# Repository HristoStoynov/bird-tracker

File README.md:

# Bird Tracker

A lightweight GPS + cellular wildlife tracker built around the STM32U031, SIM7080G (NB-IoT/LTE-M), and u-blox SAM-M10Q GNSS module.

## Repository structure

```
firmware/   STM32 firmware
hardware/   KiCad schematics and PCB layout
```

> More updates coming July 2026.

## License

MIT — see [LICENSE](LICENSE).

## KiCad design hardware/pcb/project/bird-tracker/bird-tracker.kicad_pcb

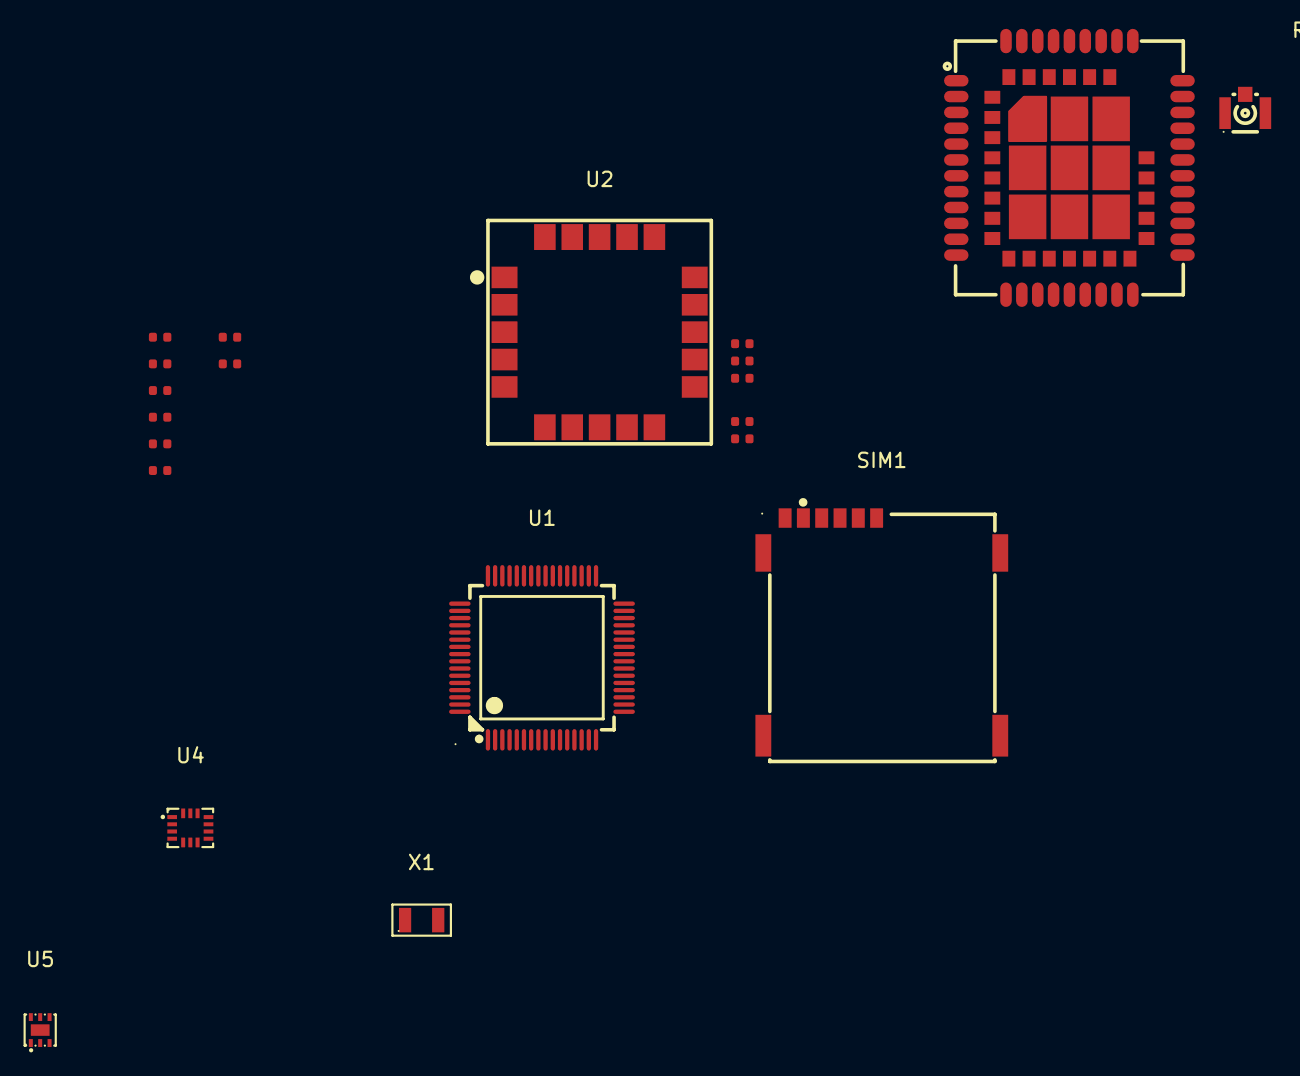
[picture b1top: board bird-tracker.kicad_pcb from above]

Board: 2 copper layers, 21 parts (0 on the bottom side), 9 nets, no tracks yet.

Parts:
C1, C2, C3, C5: 100nF; C_0402
C4: 10uF; C_0402
R1: 22Ω; R_0402
R2, R3: 2.2kΩ; R_0402
R2#2, R3#2, R4: 22kΩ; R_0402
R5, R6: 10kΩ; R_0402
RF1: U.FL-R-SMT; ANT-SMD_U.FL-R-SMT10
SIM1: MICRO SIM 6P H1.35; SIM-SMD_MICRO-SIM-6P-H1.35
U1: STM32U031R8T6; LQFP-64_L10.0-W10.0-P0.50-LS12.0-BL
U2: SAM-M10Q-00B; LCC-20_L15.5-W15.5-P1.90_SAM-M10Q-00B
U3: SIM7080G; LCC-SMD_SIM7080G
U4: LSM6DS3TR; LGA-14_L3.0-W2.5-P0.50-TL
U5: STTS22HTR; DFN-6_L2.0-W2.0-P0.65-BL-EP1.2
X1: ABS07-32.768KHZ-7-T; OSC-SMD_L3.2-W1.5

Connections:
+3.3V: C1.1, C2.1, C3.1, C4.1, C5.1, R2.2, R2#2.2, R3.2, R3#2.2, R5.2, R6.1, U2.2 (V_IO), U2.17 (VCC), U4.5 (VDDIO), U4.8 (VDD), U4.12 (CS), U5.3 (VDD)
GND: C1.2, C2.2, C3.2, C4.2, C5.2, RF1.1 (GND), RF1.3 (GND), SIM1.5 (GND), SIM1.8 (GND), SIM1.9 (GND), SIM1.10 (GND), SIM1.11 (GND), U2.1 (GND), U2.4 (GND), U2.5 (GND), U2.6 (GND), U2.10 (GND), U2.11 (GND), U2.15 (GND), U2.16 (GND), U2.20 (GND), U3.8 (GND), U3.13 (GND), U3.19 (GND), U3.21 (GND), U3.27 (GND), U3.30 (GND), U3.31 (GND), U3.33 (GND), U3.36 (GND), U3.37 (GND), U3.45 (GND), U3.63 (GND), U3.66 (GND), U3.67 (GND), U3.69 (GND), U3.70 (GND), U3.71 (GND), U3.72 (GND), U3.73 (GND), U3.74 (GND), U3.75 (GND), U3.76 (GND), U3.77 (GND), U4.1 (SDO/SA0), U4.2 (SDX), U4.3 (SCX), U4.6 (GND), U4.7 (GND), U5.4 (Addr), U5.5 (GND), U5.7 (EP)
GNSS_SCL: R1.2, R2.1
GNSS_SDA: R3.1, R4.1
unnamed: RF1.2 (SIG), U3.32 (RF_ANT)
unnamed: R1.1, U2.12 (SCL)
unnamed: R4.2, U2.9 (SDA)
SENS_SCL: R6.2, U4.13 (SCL), U5.1 (SCL)
SENS_SDA: R5.1, U4.14 (SDA), U5.6 (SDA)

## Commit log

2026-06-04 Add README, license and gitignore
2026-06-04 Set up KiCAD project
    Created a KiCAD project with multiple schematics. Imported all components for the MCU, GNSS, Sensors and SIM schematics' sheets.
2026-06-06 Sensors sheet complete
    Revision v0.1
2026-06-06 GNSS sheet complete
    Revision v0.1
2026-06-12 SIM sheet complete
